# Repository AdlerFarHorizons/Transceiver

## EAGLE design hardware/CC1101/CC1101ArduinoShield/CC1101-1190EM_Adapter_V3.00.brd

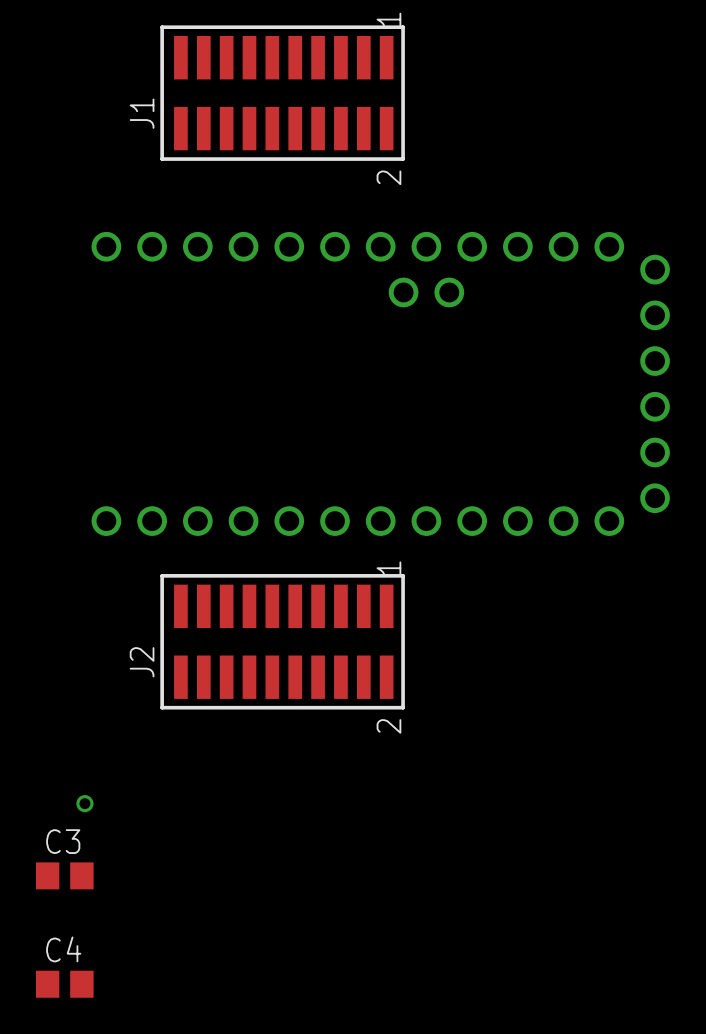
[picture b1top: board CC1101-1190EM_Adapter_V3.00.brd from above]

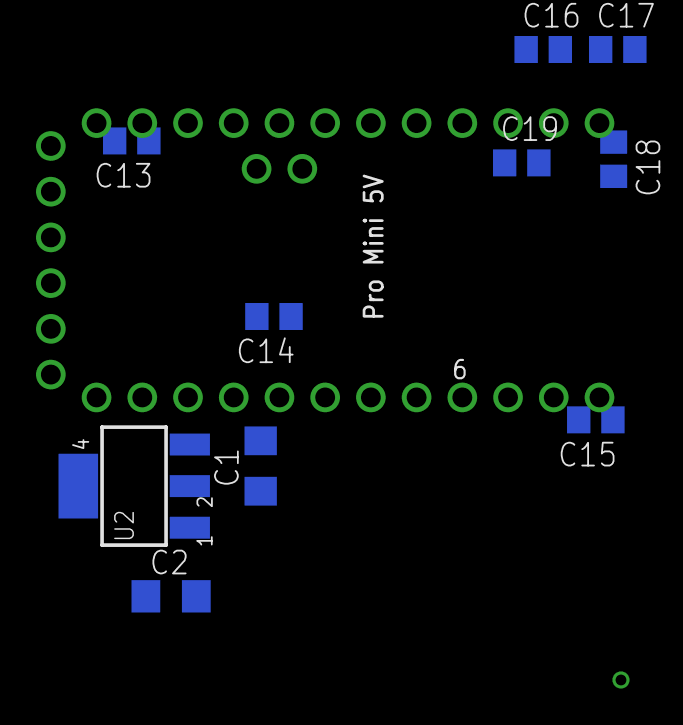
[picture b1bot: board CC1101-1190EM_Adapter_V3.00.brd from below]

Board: 2 copper layers, 16 parts (11 on the bottom side), 11 nets, no tracks yet.

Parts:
C1: 22uF; C1206
C2: 10uF; C1206
C3, C4, C13, C14, C15, C16, C17, C18, C19: 33pF; C0805
J1, J2: 20021121-00010T4LF; PINHDR10X2_50X50MIL_SMT
U2: RT9164A; TO223
U$1: ARDUINOMINI
VIA89: GND_VIA_NO_THERMAL; VIA_NO_THERMAL

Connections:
CS: C19.1, J1.P$14, U$1.P$30
GDO0: C14.1, J1.P$10, U$1.P$5, U$1.P$8
GDO2: J1.P$12, U$1.P$1
GND: C1.2, C2.2, C3.2, C4.2, C13.2, C14.2, C15.2, C16.2, C17.2, C18.2, C19.2, J1.P$1, J1.P$19, J2.P$2, U2.1, U$1.P$9, U$1.P$20
LNA_EN: C4.1, J1.P$7, U$1.P$2
PA_EN: C3.1, C15.1, J1.P$3, U$1.P$3
SCLK: C18.1, J1.P$16, U$1.P$27
SI: C16.1, J1.P$18, U$1.P$29
SO: C17.1, J1.P$20, U$1.P$28
VIN: C2.1, C13.1, U2.3, U$1.P$19
VOUT: C1.1, J2.P$7, J2.P$9, U2.2, U2.4

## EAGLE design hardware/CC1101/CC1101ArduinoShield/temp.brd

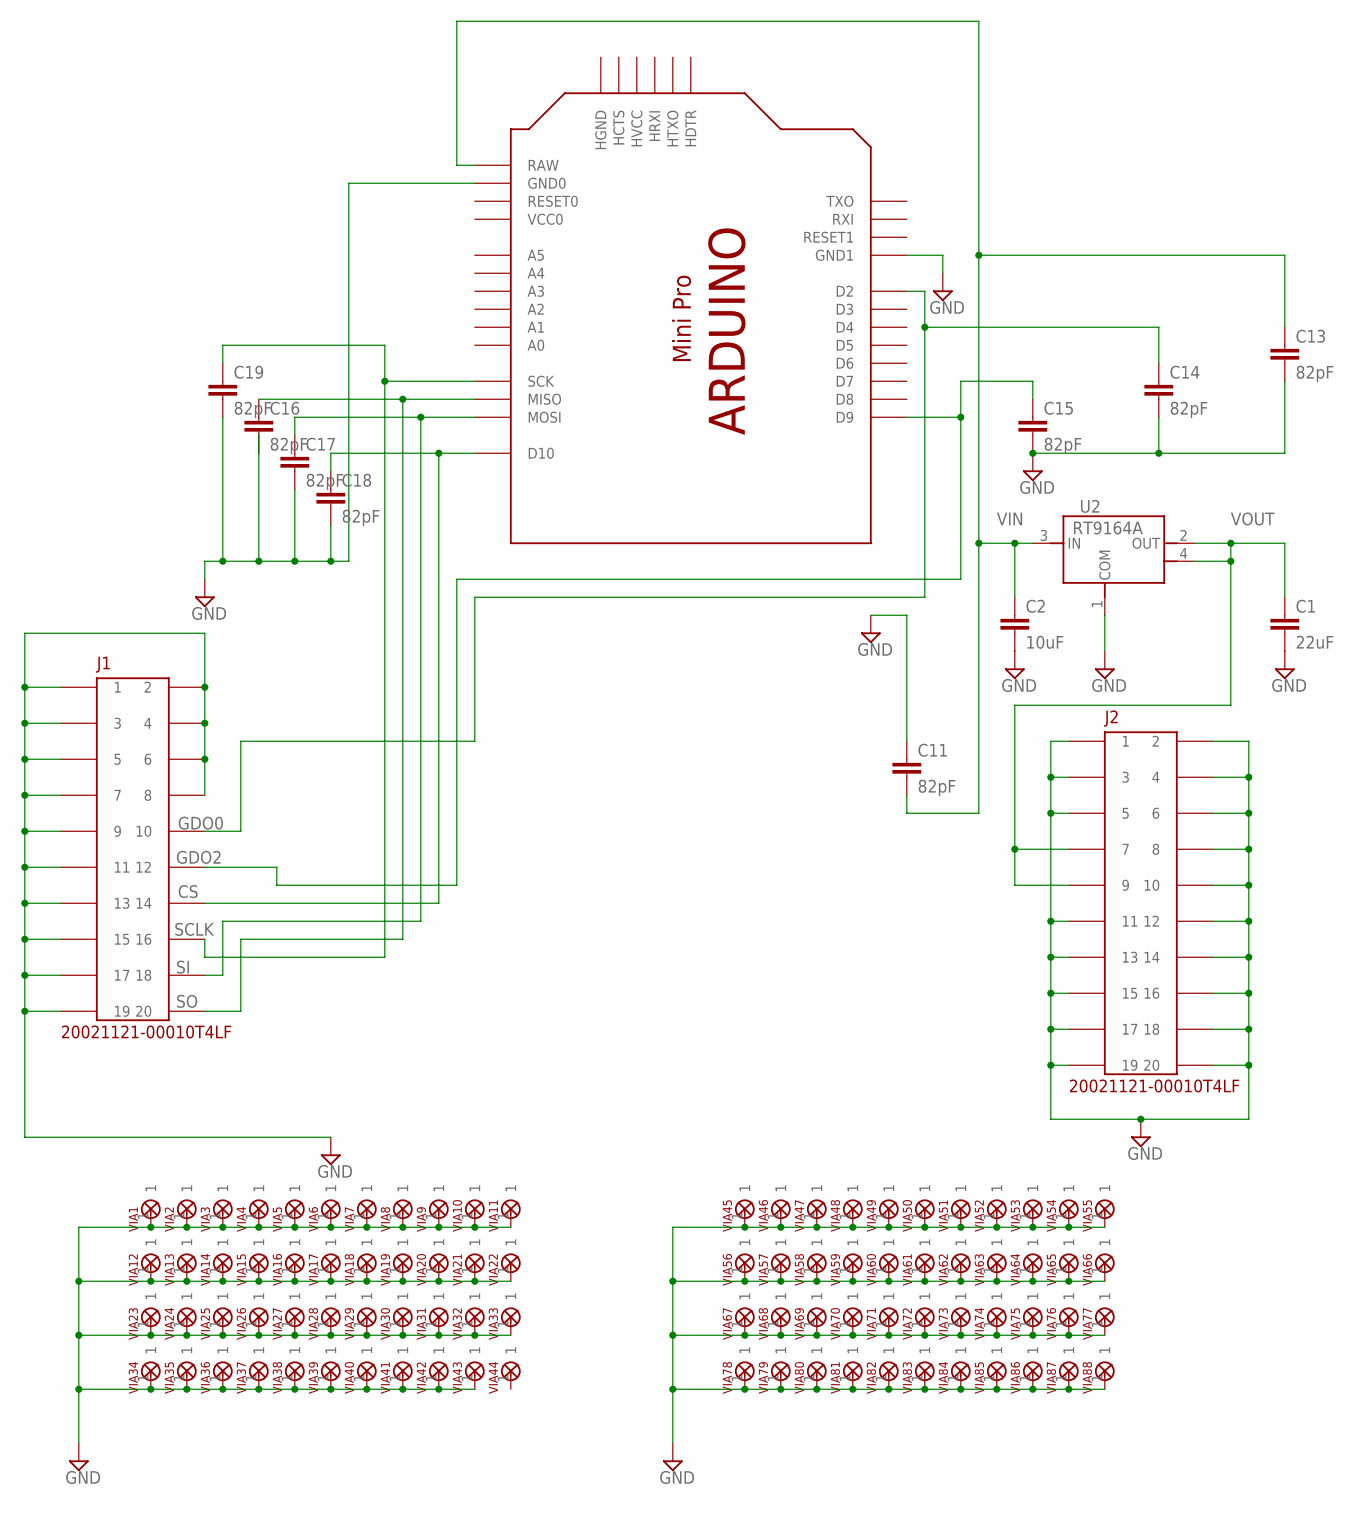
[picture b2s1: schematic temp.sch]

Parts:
C1: 22uF; C1206
C2: 10uF; C1206
C11, C13, C14, C15, C16, C17, C18, C19: 82pF; C0805
J1, J2: 20021121-00010T4LF; PINHDR10X2_50X50MIL_SMT
U2: RT9164A; TO223
U$1: ARDUINOMINI
VIA1, VIA2, VIA3, VIA4, VIA5, VIA6, VIA7, VIA8, VIA9, VIA10, VIA11, VIA12, VIA13, VIA14, VIA15, VIA16, VIA17, VIA18, VIA19, VIA20, VIA21, VIA22, VIA23, VIA24, VIA25, VIA26, VIA27, VIA28, VIA29, VIA30, VIA31, VIA32, VIA33, VIA34, VIA35, VIA36, VIA37, VIA38, VIA39, VIA40, VIA41, VIA42, VIA43, VIA44, VIA45, VIA46, VIA47, VIA48, VIA49, VIA50, VIA51, VIA52, VIA53, VIA54, VIA55, VIA56, VIA57, VIA58, VIA59, VIA60, VIA61, VIA62, VIA63, VIA64, VIA65, VIA66, VIA67, VIA68, VIA69, VIA70, VIA71, VIA72, VIA73, VIA74, VIA75, VIA76, VIA77, VIA78, VIA79, VIA80, VIA81, VIA82, VIA83, VIA84, VIA85, VIA86, VIA87, VIA88: GND_VIA_NO_THERMAL; VIA_NO_THERMAL

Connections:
CS: C18.1, J1.P$14 (14), U$1.P$30 (D10)
GDO0: C14.1, J1.P$10 (10), U$1.P$8 (D2)
GDO2: C15.1, J1.P$12 (12), U$1.P$1 (D9)
GND: C1.2, C2.2, C11.1, C13.2, C14.2, C15.2, C17.2, C18.2, C19.2, J1.P$1 (1), J1.P$2 (2), J1.P$3 (3), J1.P$4 (4), J1.P$5 (5), J1.P$6 (6), J1.P$7 (7), J1.P$8 (8), J1.P$9 (9), J1.P$11 (11), J1.P$13 (13), J1.P$15 (15), J1.P$17 (17), J1.P$19 (19), J2.P$1 (1), J2.P$2 (2), J2.P$3 (3), J2.P$4 (4), J2.P$5 (5), J2.P$6 (6), J2.P$8 (8), J2.P$10 (10), J2.P$11 (11), J2.P$12 (12), J2.P$13 (13), J2.P$14 (14), J2.P$15 (15), J2.P$16 (16), J2.P$17 (17), J2.P$18 (18), J2.P$19 (19), J2.P$20 (20), U2.1 (COM), U$1.P$9 (GND1), U$1.P$20 (GND0), VIA1.1, VIA2.1, VIA3.1, VIA4.1, VIA5.1, VIA6.1, VIA7.1, VIA8.1, VIA9.1, VIA10.1, VIA11.1, VIA12.1, VIA13.1, VIA14.1, VIA15.1, VIA16.1, VIA17.1, VIA18.1, VIA19.1, VIA20.1, VIA21.1, VIA22.1, VIA23.1, VIA24.1, VIA25.1, VIA26.1, VIA27.1, VIA28.1, VIA29.1, VIA30.1, VIA31.1, VIA32.1, VIA33.1, VIA34.1, VIA35.1, VIA36.1, VIA37.1, VIA38.1, VIA39.1, VIA40.1, VIA41.1, VIA42.1, VIA43.1, VIA45.1, VIA46.1, VIA47.1, VIA48.1, VIA49.1, VIA50.1, VIA51.1, VIA52.1, VIA53.1, VIA54.1, VIA55.1, VIA56.1, VIA57.1, VIA58.1, VIA59.1, VIA60.1, VIA61.1, VIA62.1, VIA63.1, VIA64.1, VIA65.1, VIA66.1, VIA67.1, VIA68.1, VIA69.1, VIA70.1, VIA71.1, VIA72.1, VIA73.1, VIA74.1, VIA75.1, VIA76.1, VIA77.1, VIA78.1, VIA79.1, VIA80.1, VIA81.1, VIA82.1, VIA83.1, VIA84.1, VIA85.1, VIA86.1, VIA87.1, VIA88.1
SCLK: C19.1, J1.P$16 (16), U$1.P$27 (SCK)
SI: C17.1, J1.P$18 (18), U$1.P$29 (MOSI)
SO: C16.1, J1.P$20 (20), U$1.P$28 (MISO)
VIN: C2.1, C11.2, C13.1, U2.3 (IN), U$1.P$19 (RAW)
VOUT: C1.1, J2.P$7 (7), J2.P$9 (9), U2.2 (OUT), U2.4 (OUT)

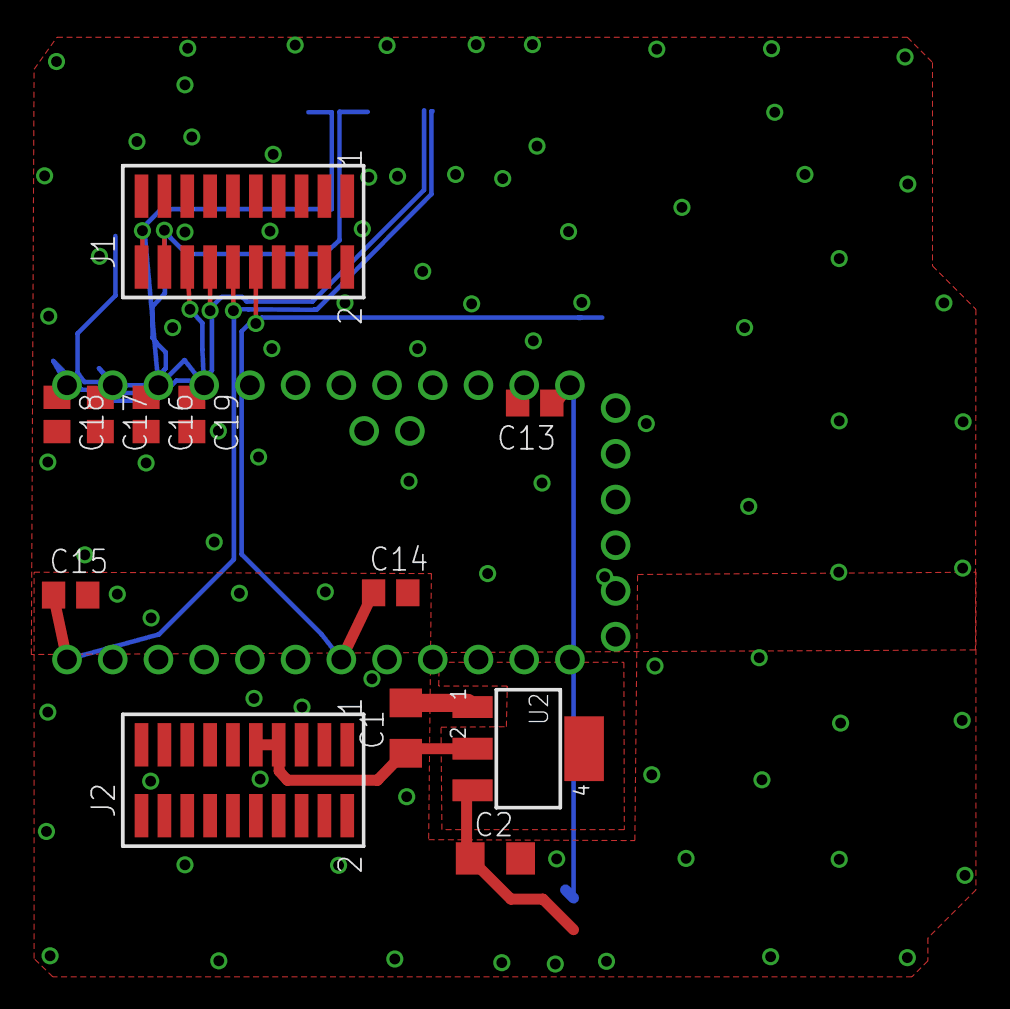
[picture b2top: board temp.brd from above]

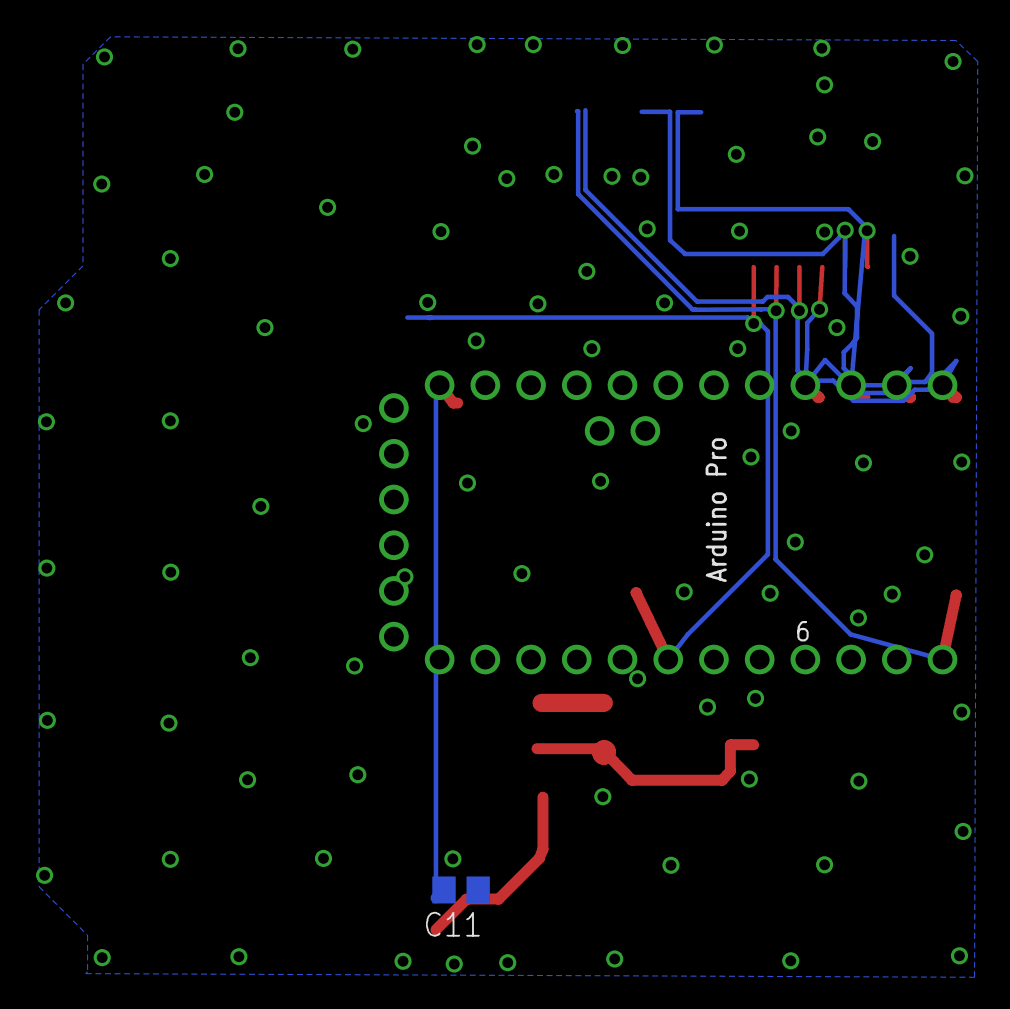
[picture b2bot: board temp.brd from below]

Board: 2 copper layers, 102 parts (2 on the bottom side), 9 nets.

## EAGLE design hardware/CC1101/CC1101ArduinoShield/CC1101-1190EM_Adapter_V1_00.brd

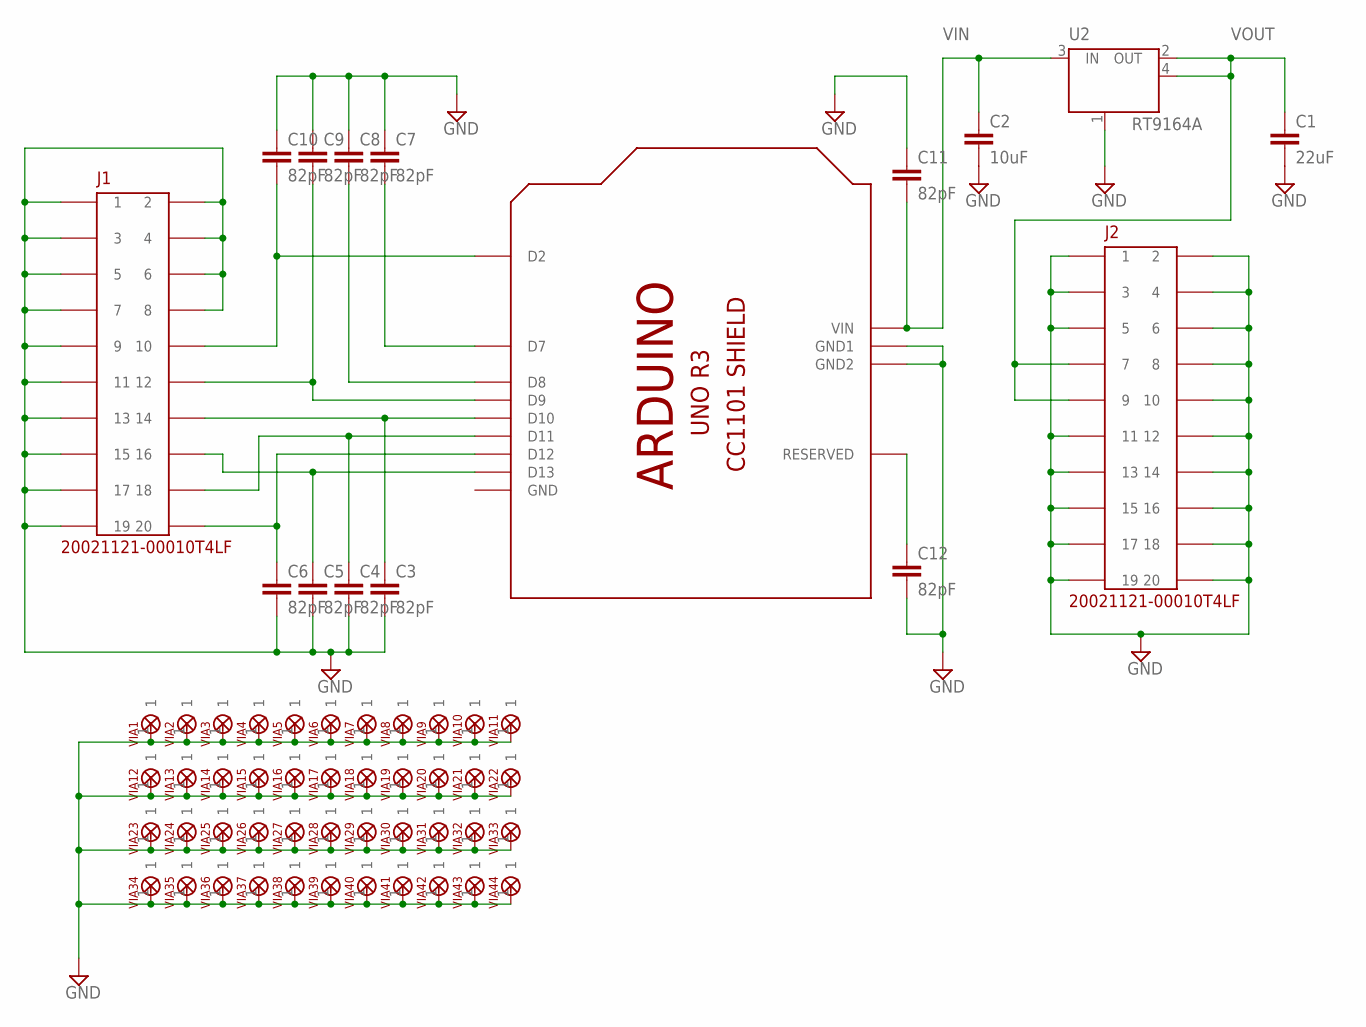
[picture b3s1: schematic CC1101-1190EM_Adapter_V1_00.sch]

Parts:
C1: 22uF; C1206
C2: 10uF; C1206
C3, C4, C5, C6, C7, C8, C9, C10, C11, C12: 82pF; C0805
J1, J2: 20021121-00010T4LF; PINHDR10X2_50X50MIL_SMT
U1: SHIELD-UNOR3-CC1101
U2: RT9164A; TO223
VIA1, VIA2, VIA3, VIA4, VIA5, VIA6, VIA7, VIA8, VIA9, VIA10, VIA11, VIA12, VIA13, VIA14, VIA15, VIA16, VIA17, VIA18, VIA19, VIA20, VIA21, VIA22, VIA23, VIA24, VIA25, VIA26, VIA27, VIA28, VIA29, VIA30, VIA31, VIA32, VIA33, VIA34, VIA35, VIA36, VIA37, VIA38, VIA39, VIA40, VIA41, VIA42, VIA43, VIA44: GND_VIA_NO_THERMAL; VIA_NO_THERMAL

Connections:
GND: C1.2, C2.2, C3.2, C4.2, C5.2, C6.2, C7.1, C8.1, C9.1, C10.1, C11.1, C12.2, J1.P$1 (1), J1.P$2 (2), J1.P$3 (3), J1.P$4 (4), J1.P$5 (5), J1.P$6 (6), J1.P$7 (7), J1.P$8 (8), J1.P$9 (9), J1.P$11 (11), J1.P$13 (13), J1.P$15 (15), J1.P$17 (17), J1.P$19 (19), J2.P$1 (1), J2.P$2 (2), J2.P$3 (3), J2.P$4 (4), J2.P$5 (5), J2.P$6 (6), J2.P$8 (8), J2.P$10 (10), J2.P$11 (11), J2.P$12 (12), J2.P$13 (13), J2.P$14 (14), J2.P$15 (15), J2.P$16 (16), J2.P$17 (17), J2.P$18 (18), J2.P$19 (19), J2.P$20 (20), U1.GND, U1.GND1, U1.GND2, U2.1 (GND/ADJ), VIA1.1, VIA2.1, VIA3.1, VIA4.1, VIA5.1, VIA6.1, VIA7.1, VIA8.1, VIA9.1, VIA10.1, VIA11.1, VIA12.1, VIA13.1, VIA14.1, VIA15.1, VIA16.1, VIA17.1, VIA18.1, VIA19.1, VIA20.1, VIA21.1, VIA22.1, VIA23.1, VIA24.1, VIA25.1, VIA26.1, VIA27.1, VIA28.1, VIA29.1, VIA30.1, VIA31.1, VIA32.1, VIA33.1, VIA34.1, VIA35.1, VIA36.1, VIA37.1, VIA38.1, VIA39.1, VIA40.1, VIA41.1, VIA42.1, VIA43.1, VIA44.1
unnamed: C3.1, J1.P$14 (14), U1.D10
unnamed: C4.1, J1.P$18 (18), U1.D11
unnamed: C6.1, J1.P$20 (20), U1.D12
unnamed: C5.1, J1.P$16 (16), U1.D13
unnamed: C10.2, J1.P$10 (10), U1.D2
unnamed: C9.2, J1.P$12 (12), U1.D9
unnamed: C8.2, U1.D8
unnamed: C7.2, U1.D7
unnamed: C12.1, U1.RESERVED
VIN: C2.1, C11.2, U1.VIN, U2.3 (IN)
VOUT: C1.1, J2.P$7 (7), J2.P$9 (9), U2.2 (OUT), U2.4 (OUT)

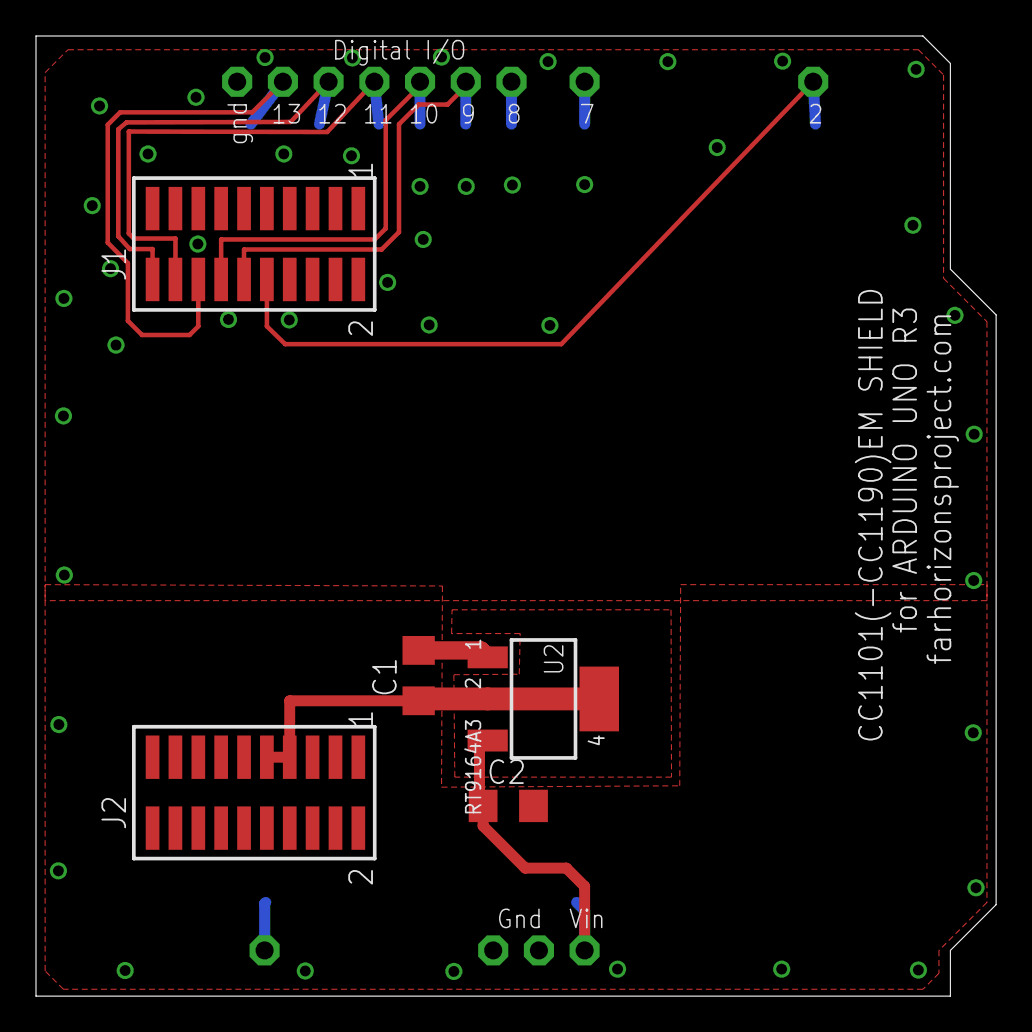
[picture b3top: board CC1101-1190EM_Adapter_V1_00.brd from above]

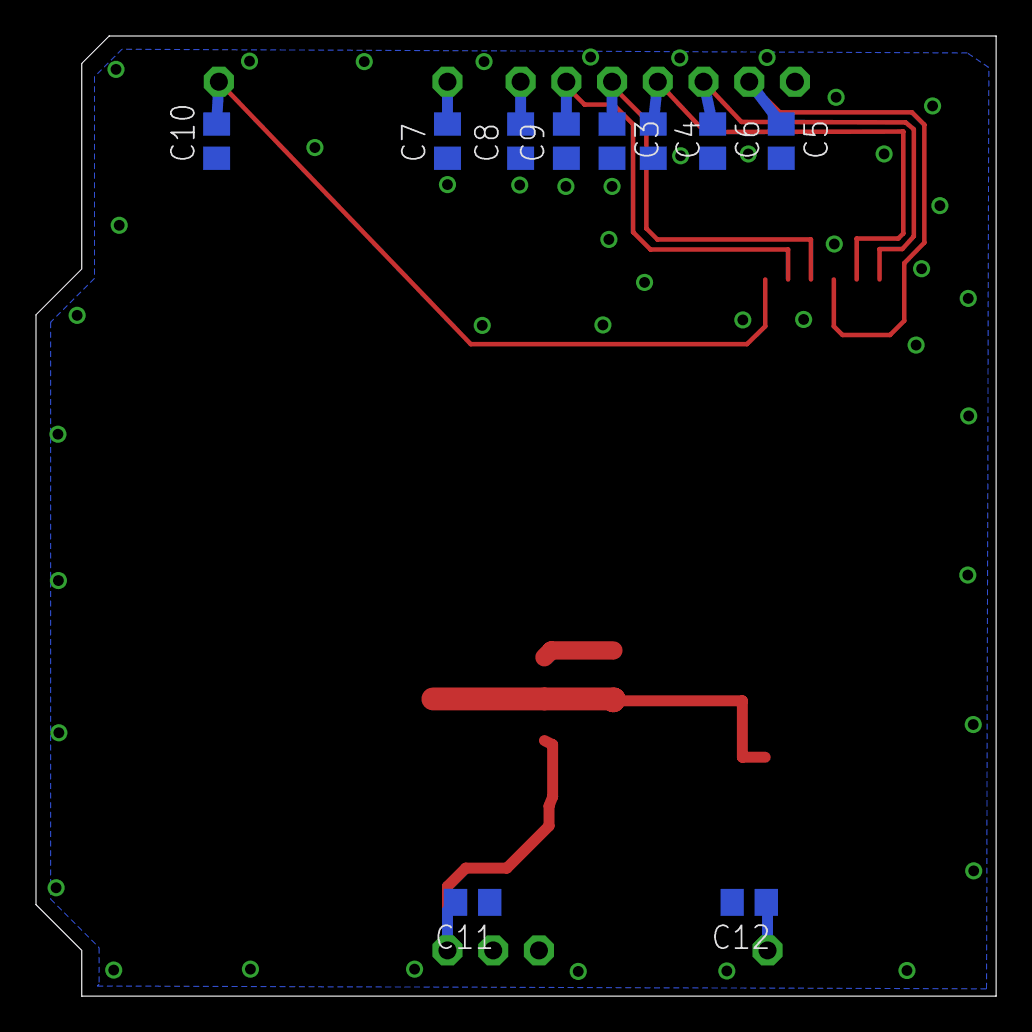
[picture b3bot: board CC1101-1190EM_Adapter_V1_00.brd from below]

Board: 2 copper layers, 53.3 x 53.3 mm, 60 parts (10 on the bottom side), 12 nets.

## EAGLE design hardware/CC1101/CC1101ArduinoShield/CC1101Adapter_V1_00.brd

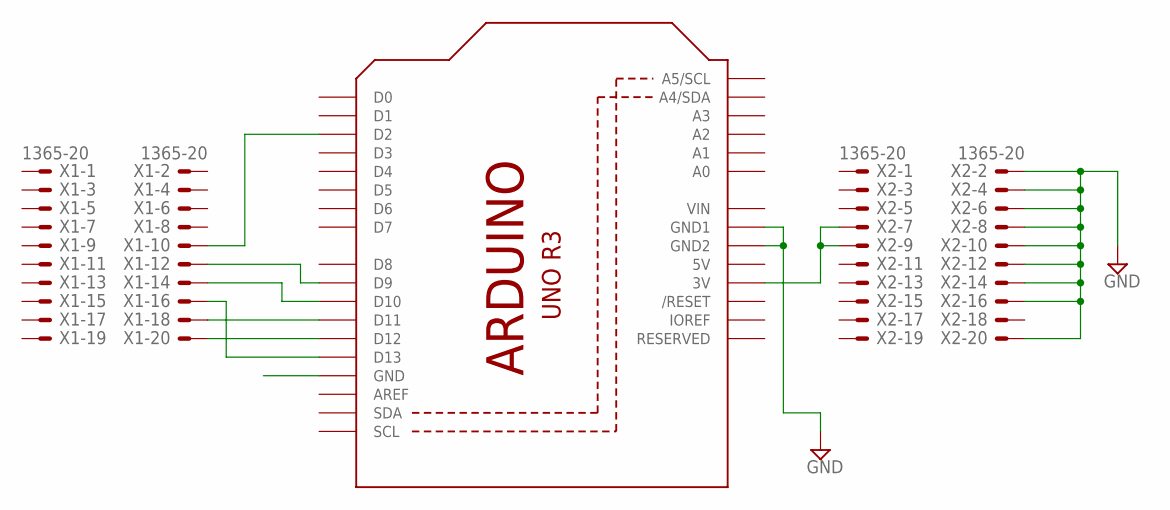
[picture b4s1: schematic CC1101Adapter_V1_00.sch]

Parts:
U1: ARDUINOR3-DIMENSION; ARDUINOR3
X1, X2: 1365-20

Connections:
5V: U1.5V
GND: U1.GND1, U1.GND2, X2.2, X2.4, X2.6, X2.8, X2.10, X2.12, X2.14, X2.16, X2.20
unnamed: U1.D10, X1.14
unnamed: U1.D11, X1.18
unnamed: U1.D12, X1.20
unnamed: U1.D13, X1.16
unnamed: U1.D2, X1.10
unnamed: U1.D9, X1.12
unnamed: U1.3V, X2.7, X2.9
VIN: U1.VIN

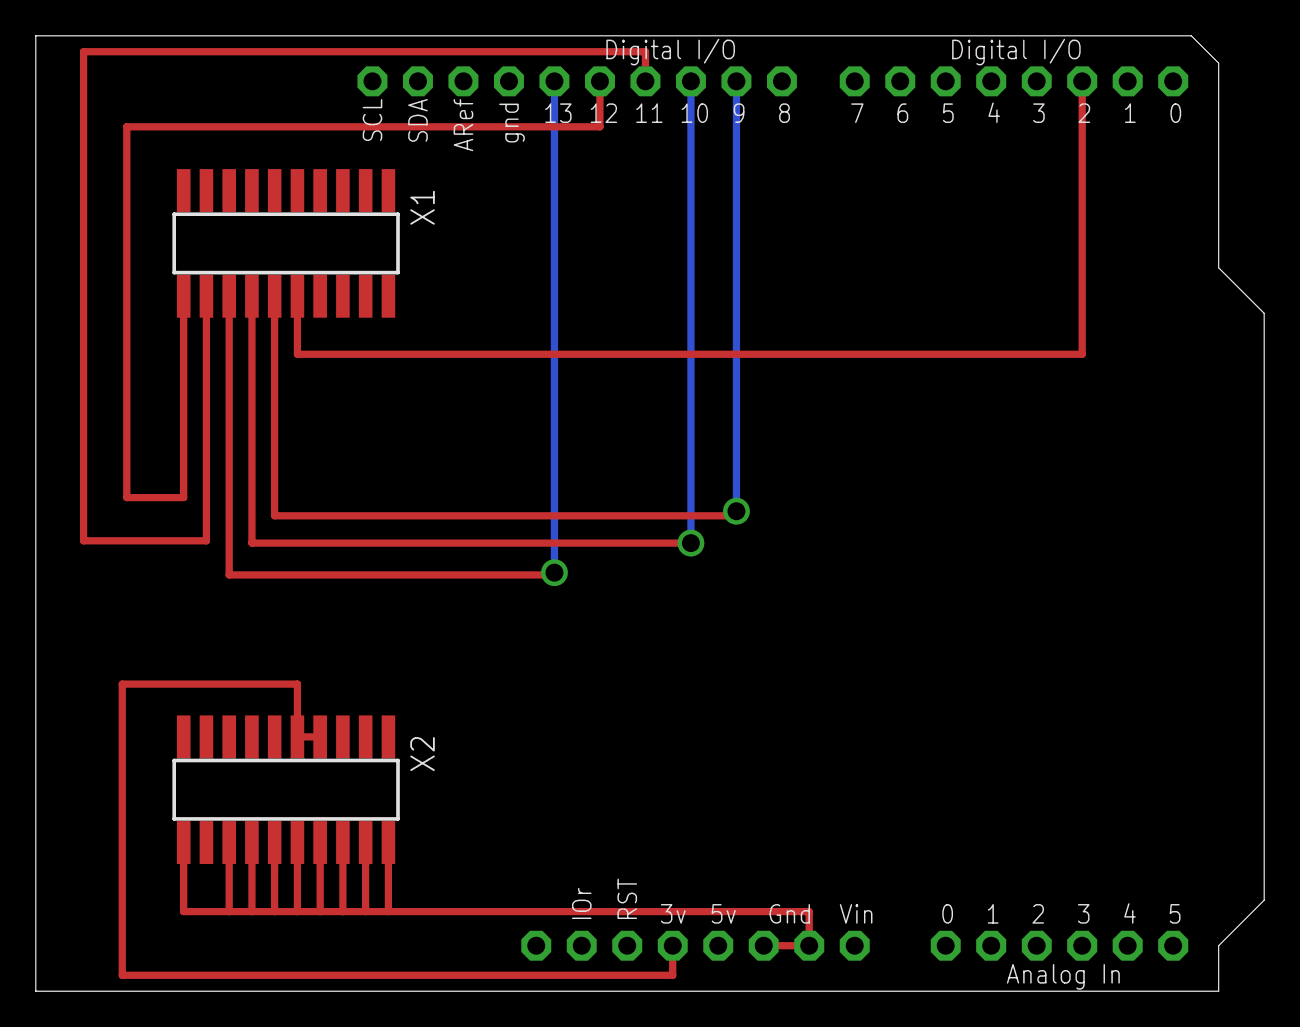
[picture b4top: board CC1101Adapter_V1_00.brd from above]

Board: 2 copper layers, 68.6 x 53.3 mm, 3 parts (0 on the bottom side), 8 nets.

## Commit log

2014-06-10 Initial commit.
2014-06-16 Remove wiki; stop ignoring scratchpad; developing CC1101 cal in scratchpad.
2014-06-24 Documentation
2014-06-24 Adding CC1101 adapter PCB designs.
2014-06-24 Forgot a file.
2014-06-24 Basic CC1101 frequency error measurement using GPS PPS as reference.
2014-06-24 A test program for external counter interrupts.
2014-12-03 Update a bunch of stuff
2014-12-10 Some Modifications to ScanRSSI
2014-12-10 Tyler's modifications to scan program
2014-12-10 Mask & Shift
2014-12-10 Printing freq values
2014-12-10 More files
2014-12-12 Light & Temp
2015-07-31 Ignore GitEye file
2015-07-31 Modified for flight
2015-07-31 Modified for Dec '14 flight
2015-07-31 Basic TX RX for Digi XTend 900
2015-07-31 Double buffering for GPS (not working)
2015-07-31 Fixed the Payload file for the 5-second transmissions only, nothing done with confirmation.
    The ground worked for awhile, then I destroyed the working copy by writing over it with a bad one. But I did find the issue that caused the YYYYYYYY's to appear at the output. Description are in comm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
2015-08-01 Integrate former submodule
2015-08-04 It works.
2015-08-05 Switched the hardware connections, Arduino softserial is now controlling the transceiver, Arduino hardware serial RX reads from GPS, TX writes to data logger. Code changed to match. Should function t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
2015-12-18 Double buffering to TX prior data if GPS updating.
2015-12-20 teensyAir and teensyGround are working clones of the two original files. Serial port references have been replaced to match the teensy, the mstimer library is replaced with other interrupt function c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
2016-02-02 Rename Teensy versions consistent with prior versions.
2016-03-18 V1.0 of Comm+GPS board based on XTend and Teensy
2016-08-12 Comment changes
2016-08-12 Add Real Time Clock
2016-08-12 Logic changes
2016-08-12 Refactor buffer names
2016-08-12 Add optional debug output to terminal
2016-08-12 Add utility functions.
2016-08-13 Outputs to serial logger removed - obsolete; other minor changes.
2016-08-13 First draft is copy of Payload code.
2016-08-13 Adapt ground code to trigger TX after RX, including received packet index.
2016-08-16 Basic logging to SD card with timestamp filename.
2016-08-22 Accomodate XTend with "PIN SLEEP" enabled.
2016-12-01 Update to state of XTendTeensy at move to FHComm repo
